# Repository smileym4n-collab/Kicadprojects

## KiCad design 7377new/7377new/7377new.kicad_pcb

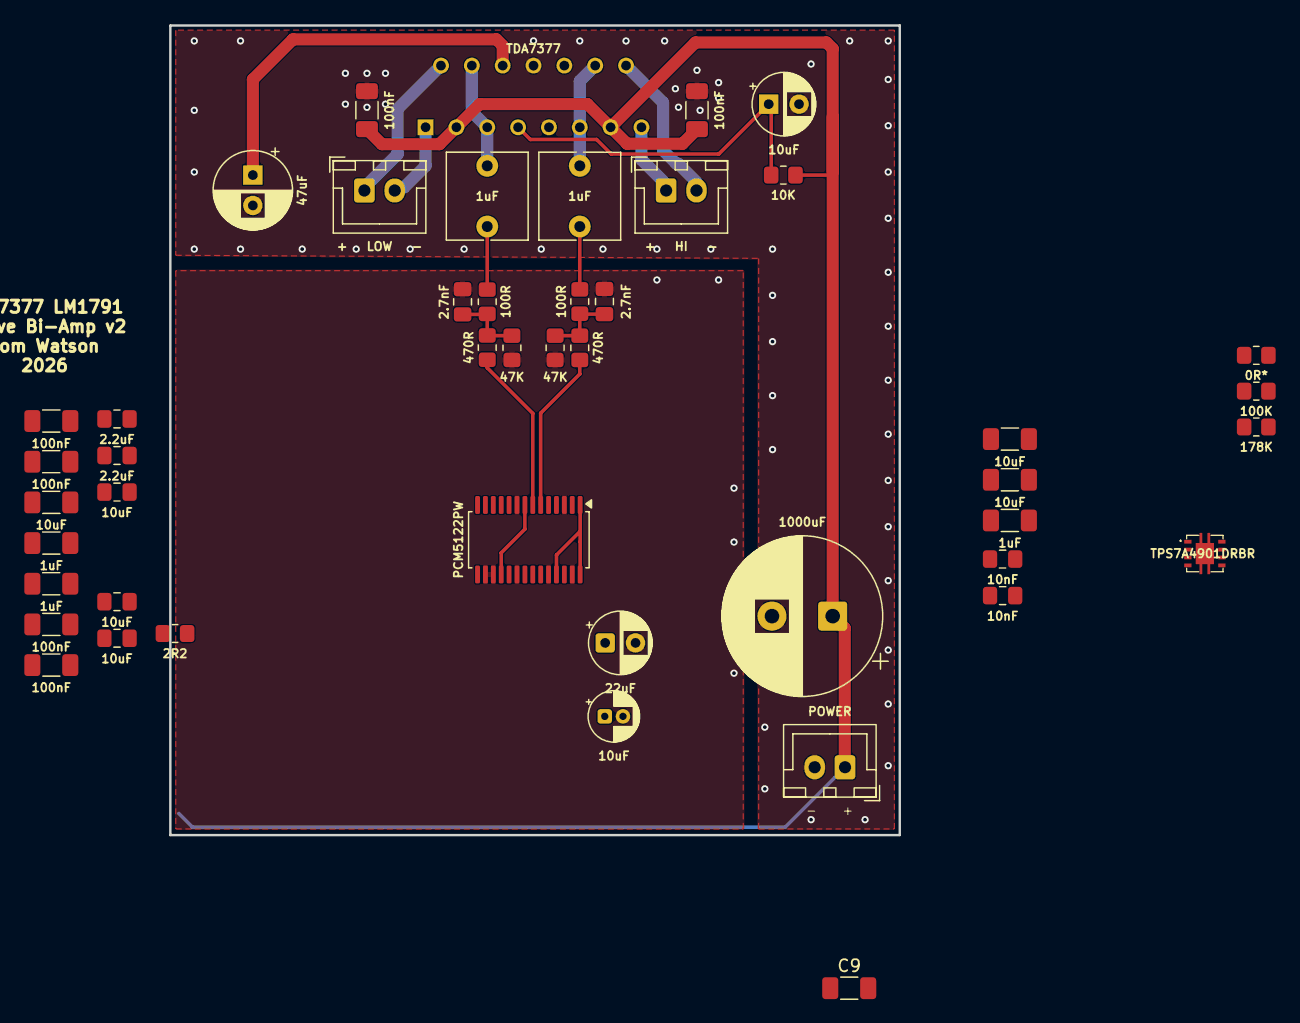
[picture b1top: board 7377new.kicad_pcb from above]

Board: 2 copper layers, 60.1 x 66.7 mm, 46 parts (0 on the bottom side), 24 nets.

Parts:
AMP1: TDA7377; AMP_TDA7377
C1, C2: 1uF; C_Rect_L7.0mm_W6.5mm_P5.00mm
C3, C9, C10, C28, C32, C66, C68: 100nF; C_1206_3216Metric_Pad1.33x1.80mm_HandSolder
C4: 1000uF; CP_Radial_D13.0mm_P5.00mm
C6, C18: 10nF; C_0805_2012Metric_Pad1.18x1.45mm_HandSolder
C11: 47uF; CP_Radial_D6.3mm_P2.50mm
C17: 10uF; CP_Radial_D5.0mm_P2.50mm
C27: 22uF; CP_Radial_D5.0mm_P2.50mm
C29, C30: 2.2uF; C_0805_2012Metric_Pad1.18x1.45mm_HandSolder
C31, C67, C69: 10uF; C_0805_2012Metric_Pad1.18x1.45mm_HandSolder
C33, C37, C39: 10uF; C_1206_3216Metric_Pad1.33x1.80mm_HandSolder
C34, C38: 2.7nF; C_0805_2012Metric_Pad1.18x1.45mm_HandSolder
C35, C36, C41: 1uF; C_1206_3216Metric_Pad1.33x1.80mm_HandSolder
C40: 10uF; CP_Radial_D4.0mm_P1.50mm
IC2: TPS7A4901DRBR
J1: + LOW -; JST_XH_B2B-XH-A_1x02_P2.50mm_Vertical
J2: + HI -; JST_XH_B2B-XH-A_1x02_P2.50mm_Vertical
J3: POWER; JST_XH_B2B-XH-A_1x02_P2.50mm_Vertical
R6, R7: 100R; R_0805_2012Metric_Pad1.20x1.40mm_HandSolder
R8, R9: 47K; R_0805_2012Metric_Pad1.20x1.40mm_HandSolder
R10: 0R*; R_0805_2012Metric_Pad1.20x1.40mm_HandSolder
R11: 100K; R_0805_2012Metric_Pad1.20x1.40mm_HandSolder
R12: 178K; R_0805_2012Metric_Pad1.20x1.40mm_HandSolder
R13: 10K; R_0805_2012Metric_Pad1.20x1.40mm_HandSolder
R31, R32: 470R; R_0805_2012Metric_Pad1.20x1.40mm_HandSolder
R61: 2R2; R_0805_2012Metric_Pad1.20x1.40mm_HandSolder
U12: PCM5122PW; TSSOP-28_4.4x9.7mm_P0.65mm

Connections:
/3V3: C18.2, C27.1, C28.1, C31.1, C39.2, C41.2, C66.1, C67.1, C68.1, C69.1, IC2.1 (OUT), R10.2, R12.2, U12.1 (CPVDD), U12.8 (AVDD), U12.18 (MODE2/MS), U12.25 (XSMT), U12.28 (DVDD)
/OUT-HI-DAC: C38.1, R7.1, R8.2, R32.1
/OUT-LOW-DAC: C34.1, R6.1, R9.2, R31.2
/VCC: AMP1.3 (VCC1), AMP1.13 (VCC2), C3.1, C4.1, C9.1, C10.1, C37.2, IC2.5 (EN), IC2.8 (IN), J3.1, R10.1, R13.2
GND: AMP1.8 (PWGND), AMP1.9 (SGND), C3.2, C4.2, C6.2, C9.2, C10.2, C11.2, C17.2, C27.2, C28.2, C29.2, C31.2, C32.2, C33.2, C34.2, C35.2, C36.2, C37.1, C38.2, C39.1, C40.2, C41.1, C66.2, C67.2, C68.2, C69.2, IC2.4 (GND), IC2.9 (EP_1), IC2.10 (EP_2), IC2.11 (EP_3), IC2.12 (EP_4), IC2.13 (EP_5), J3.2, R8.1, R9.1, R11.2, U12.3 (CPGND), U12.9 (AGND), U12.16 (ADR2/GPIO2/DOUT), U12.17 (MODE1), U12.20 (SCK), U12.24 (ADR1/MISO/FMT), U12.27 (DGND)
unnamed: AMP1.4 (IN1), AMP1.5 (IN2), C1.2
unnamed: AMP1.11 (IN4), AMP1.12 (IN3), C2.2
unnamed: AMP1.1 (OUT1), J1.2
unnamed: AMP1.2 (OUT2), J1.1
unnamed: AMP1.15 (OUT3), J2.1
unnamed: AMP1.14 (OUT4), J2.2
unnamed: AMP1.7 (STANDBY), C17.1, R13.1
unnamed: AMP1.6 (SVR), C11.1
unnamed: C1.1, R6.2
unnamed: C2.1, R7.2
unnamed: C18.1, IC2.2 (FB), R11.1, R12.1
unnamed: C6.1, IC2.6 (NR/SS)
unnamed: C36.1, C40.1, R61.2
unnamed: C30.2, U12.4 (CAPM)
unnamed: C30.1, U12.2 (CAPP)
unnamed: C32.1, C33.1, U12.26 (LDOO)
unnamed: R32.2, U12.6 (OUTL)
unnamed: R31.1, U12.7 (OUTR)
unnamed: C29.1, U12.5 (VNEG)

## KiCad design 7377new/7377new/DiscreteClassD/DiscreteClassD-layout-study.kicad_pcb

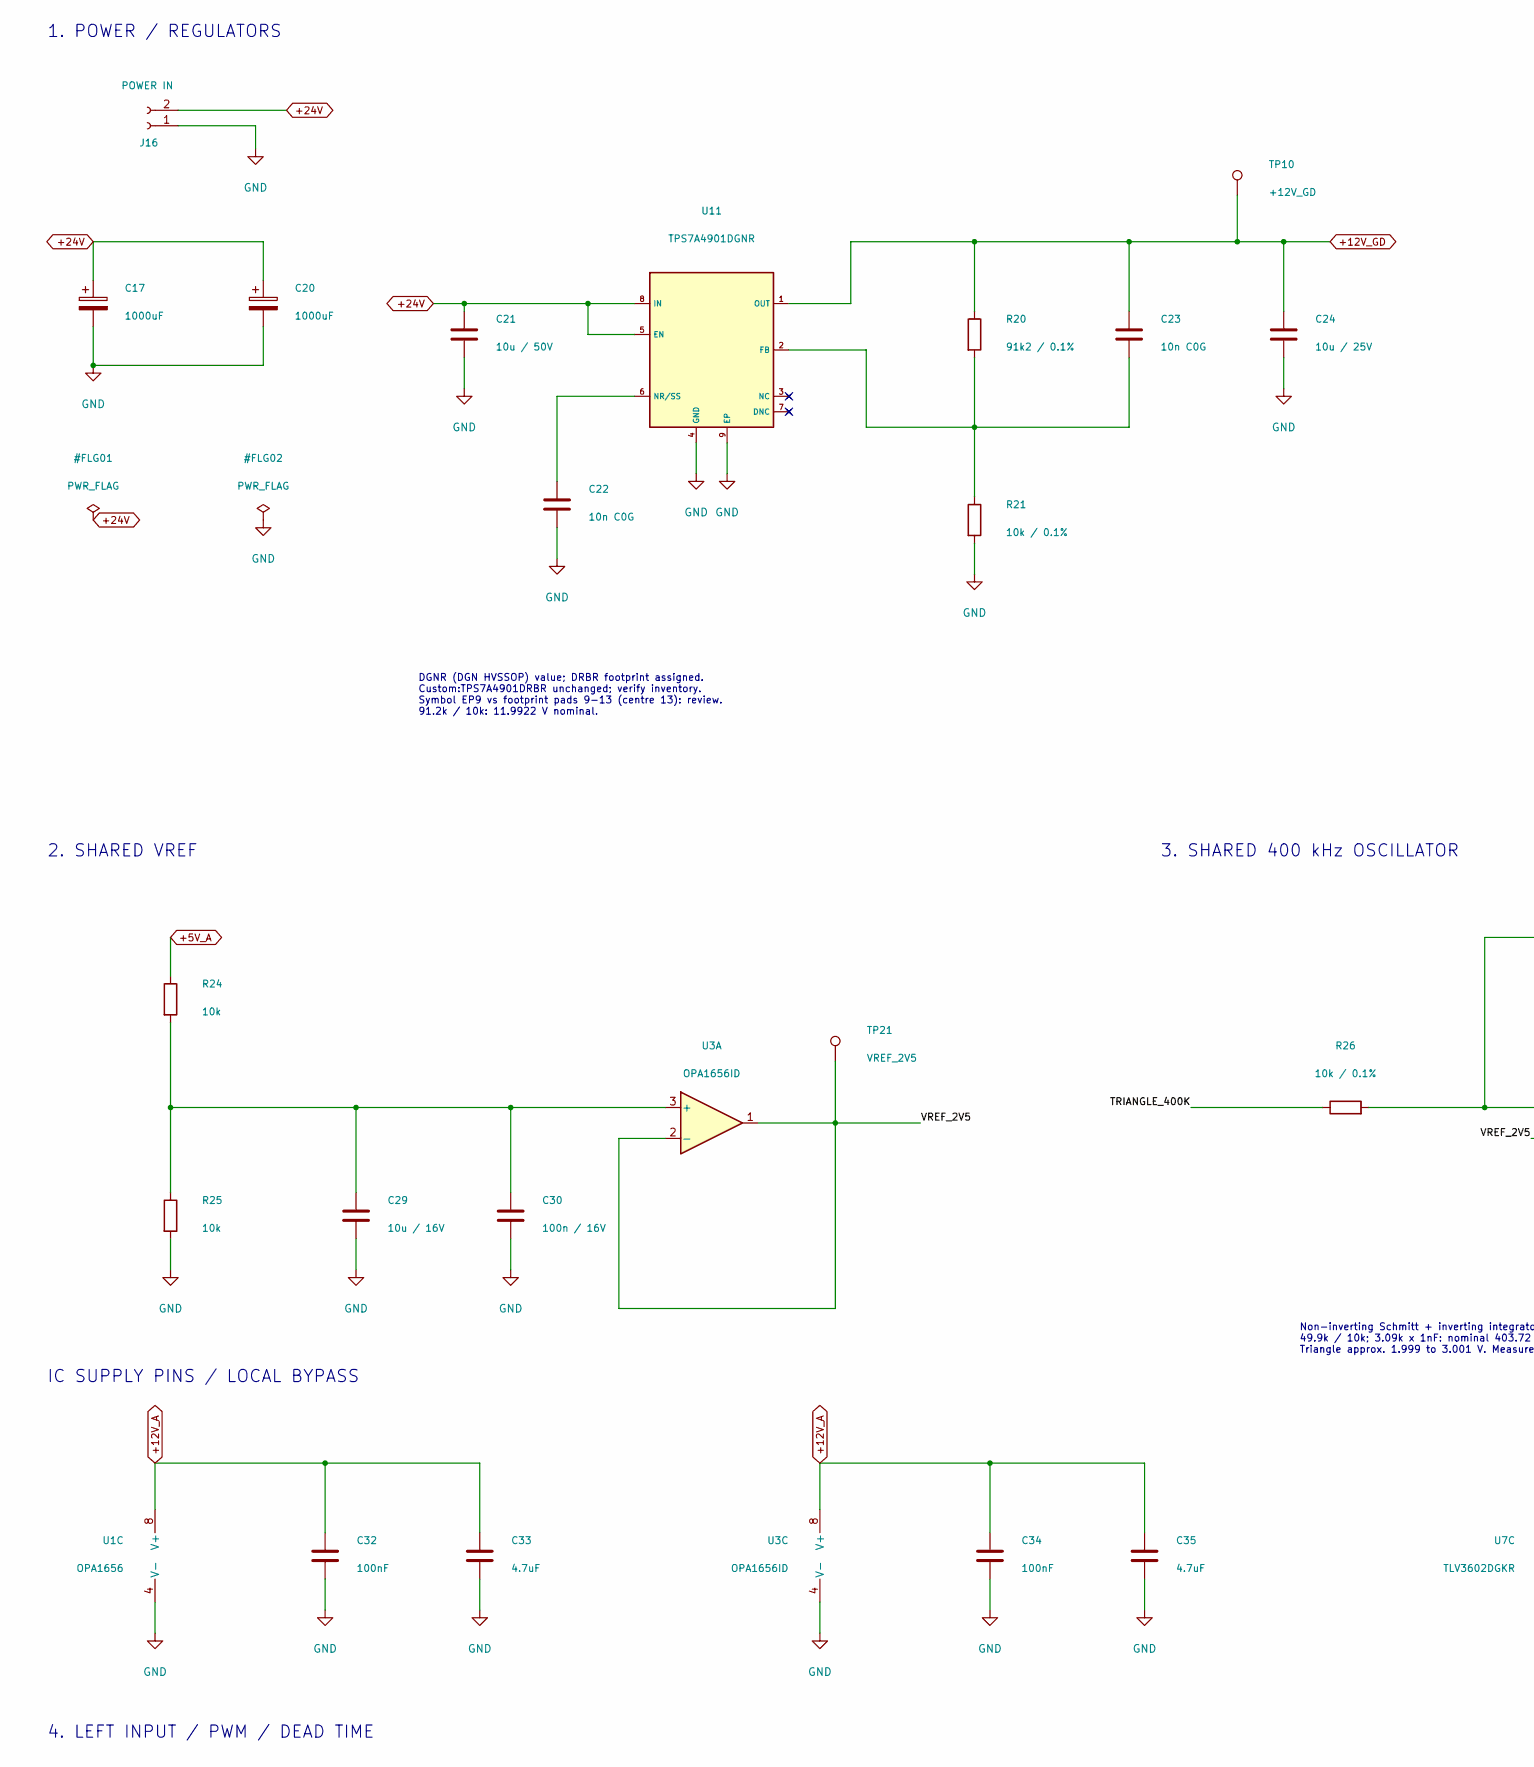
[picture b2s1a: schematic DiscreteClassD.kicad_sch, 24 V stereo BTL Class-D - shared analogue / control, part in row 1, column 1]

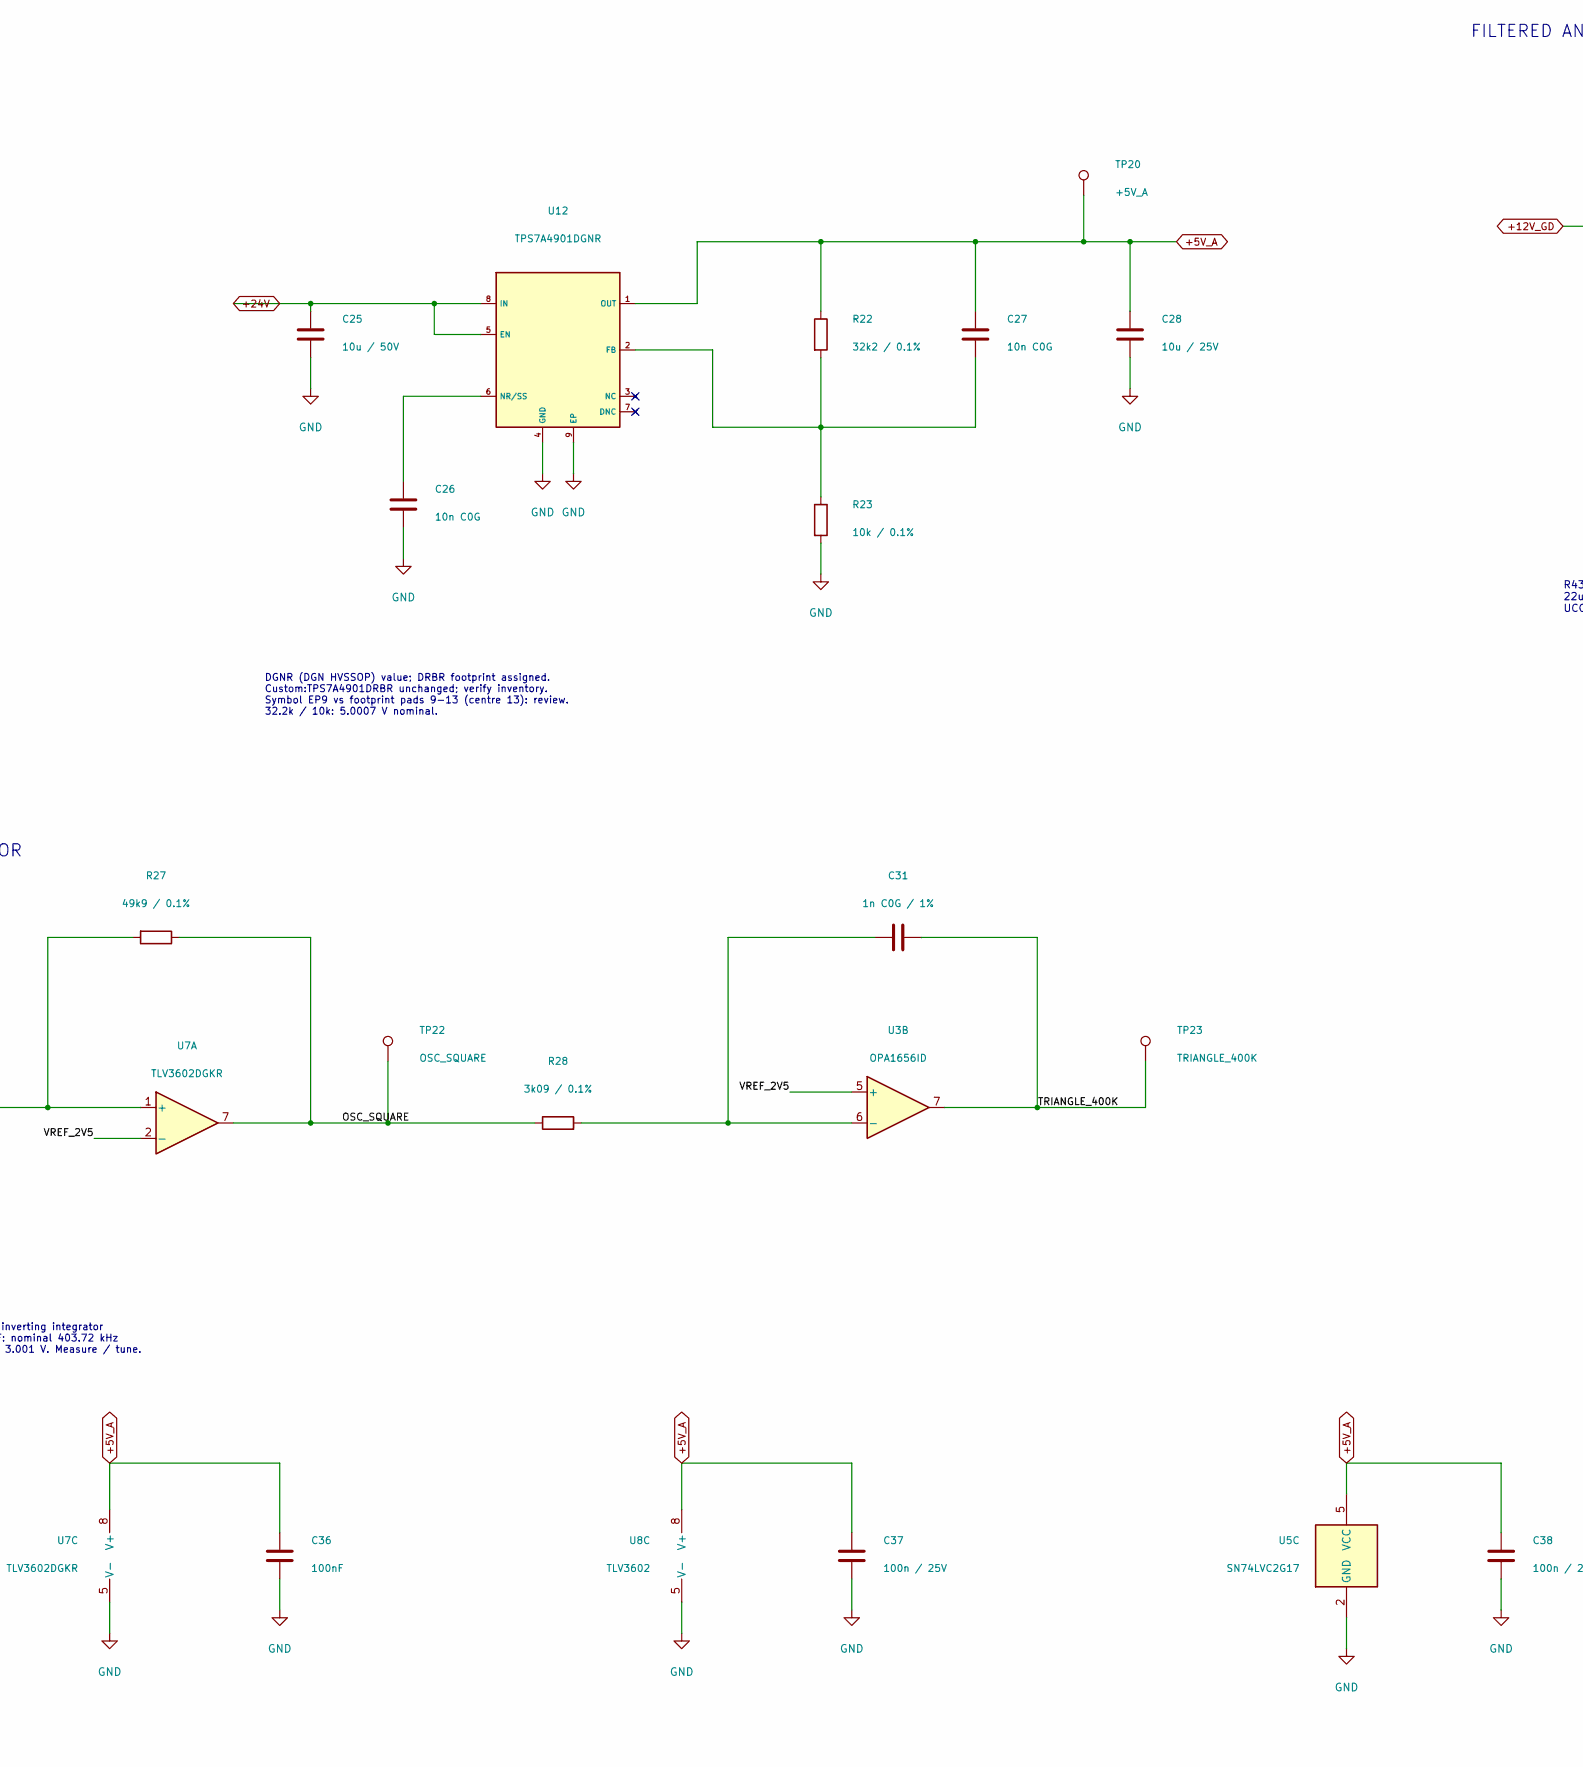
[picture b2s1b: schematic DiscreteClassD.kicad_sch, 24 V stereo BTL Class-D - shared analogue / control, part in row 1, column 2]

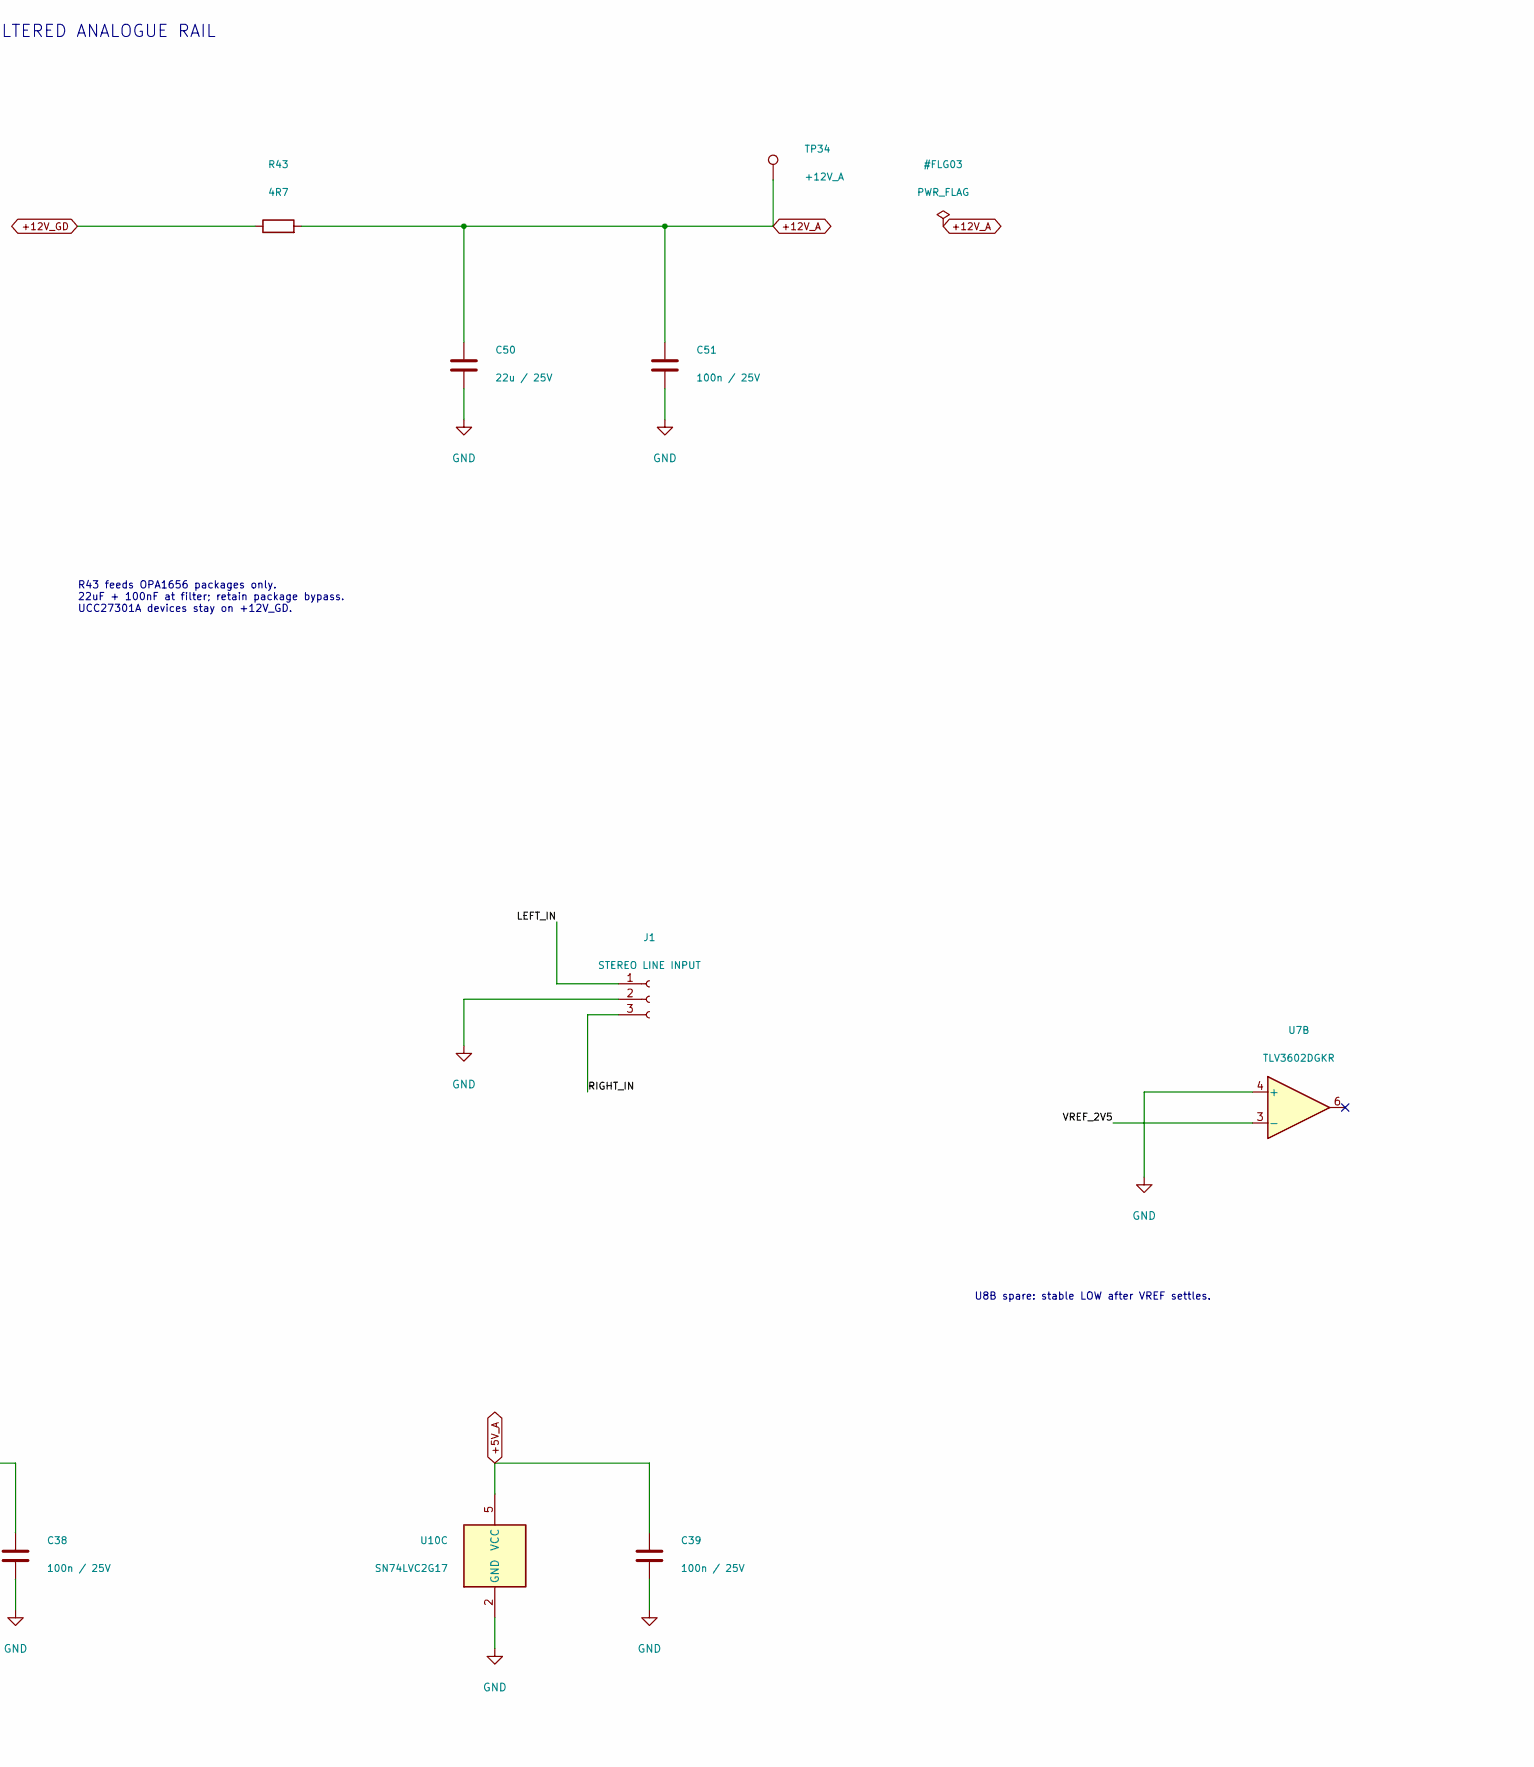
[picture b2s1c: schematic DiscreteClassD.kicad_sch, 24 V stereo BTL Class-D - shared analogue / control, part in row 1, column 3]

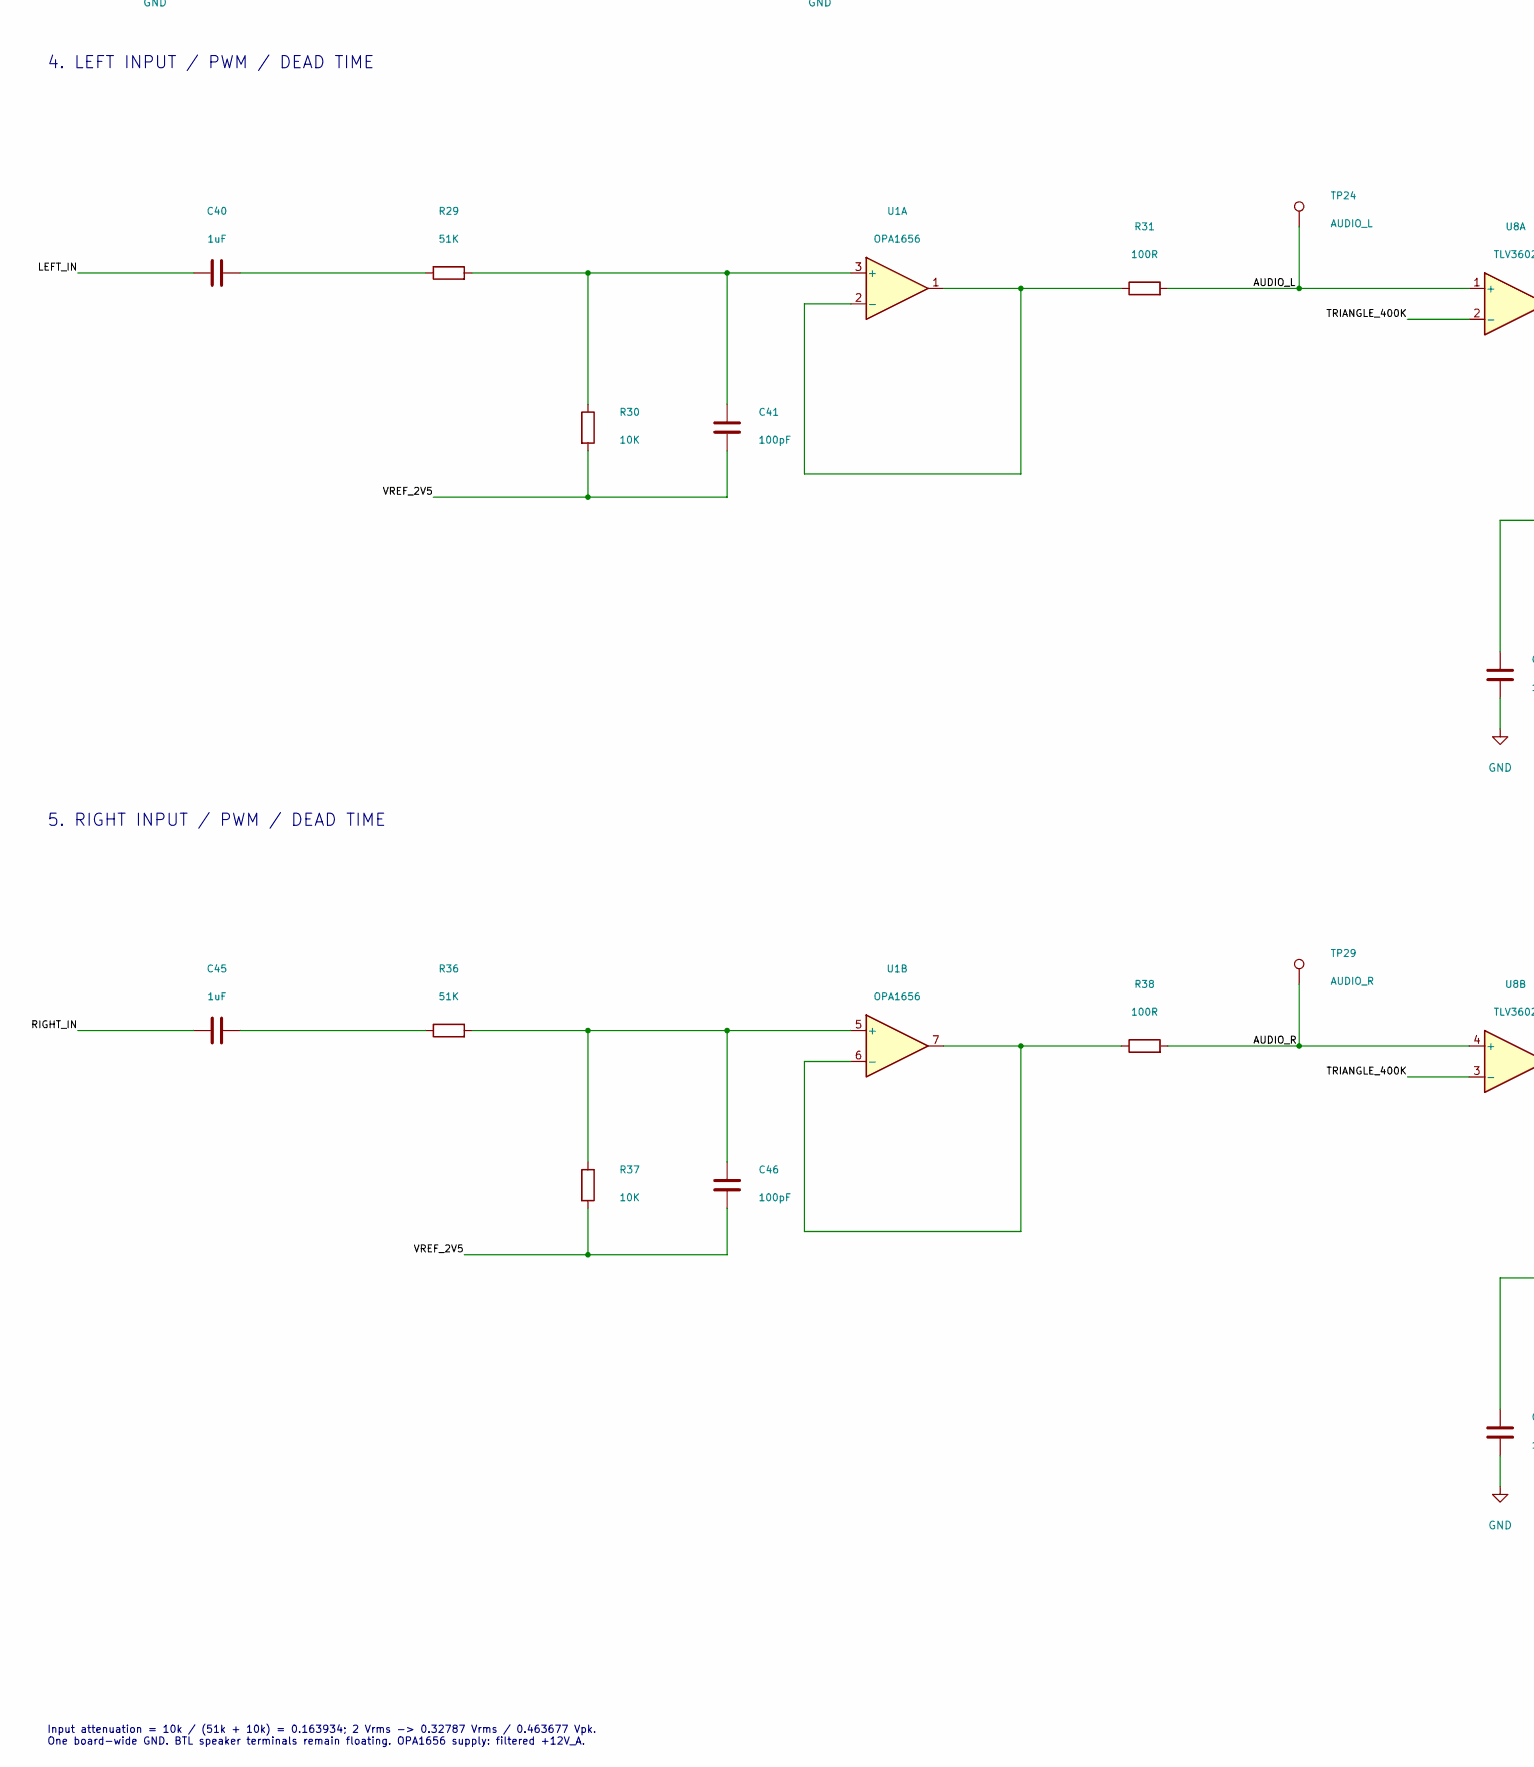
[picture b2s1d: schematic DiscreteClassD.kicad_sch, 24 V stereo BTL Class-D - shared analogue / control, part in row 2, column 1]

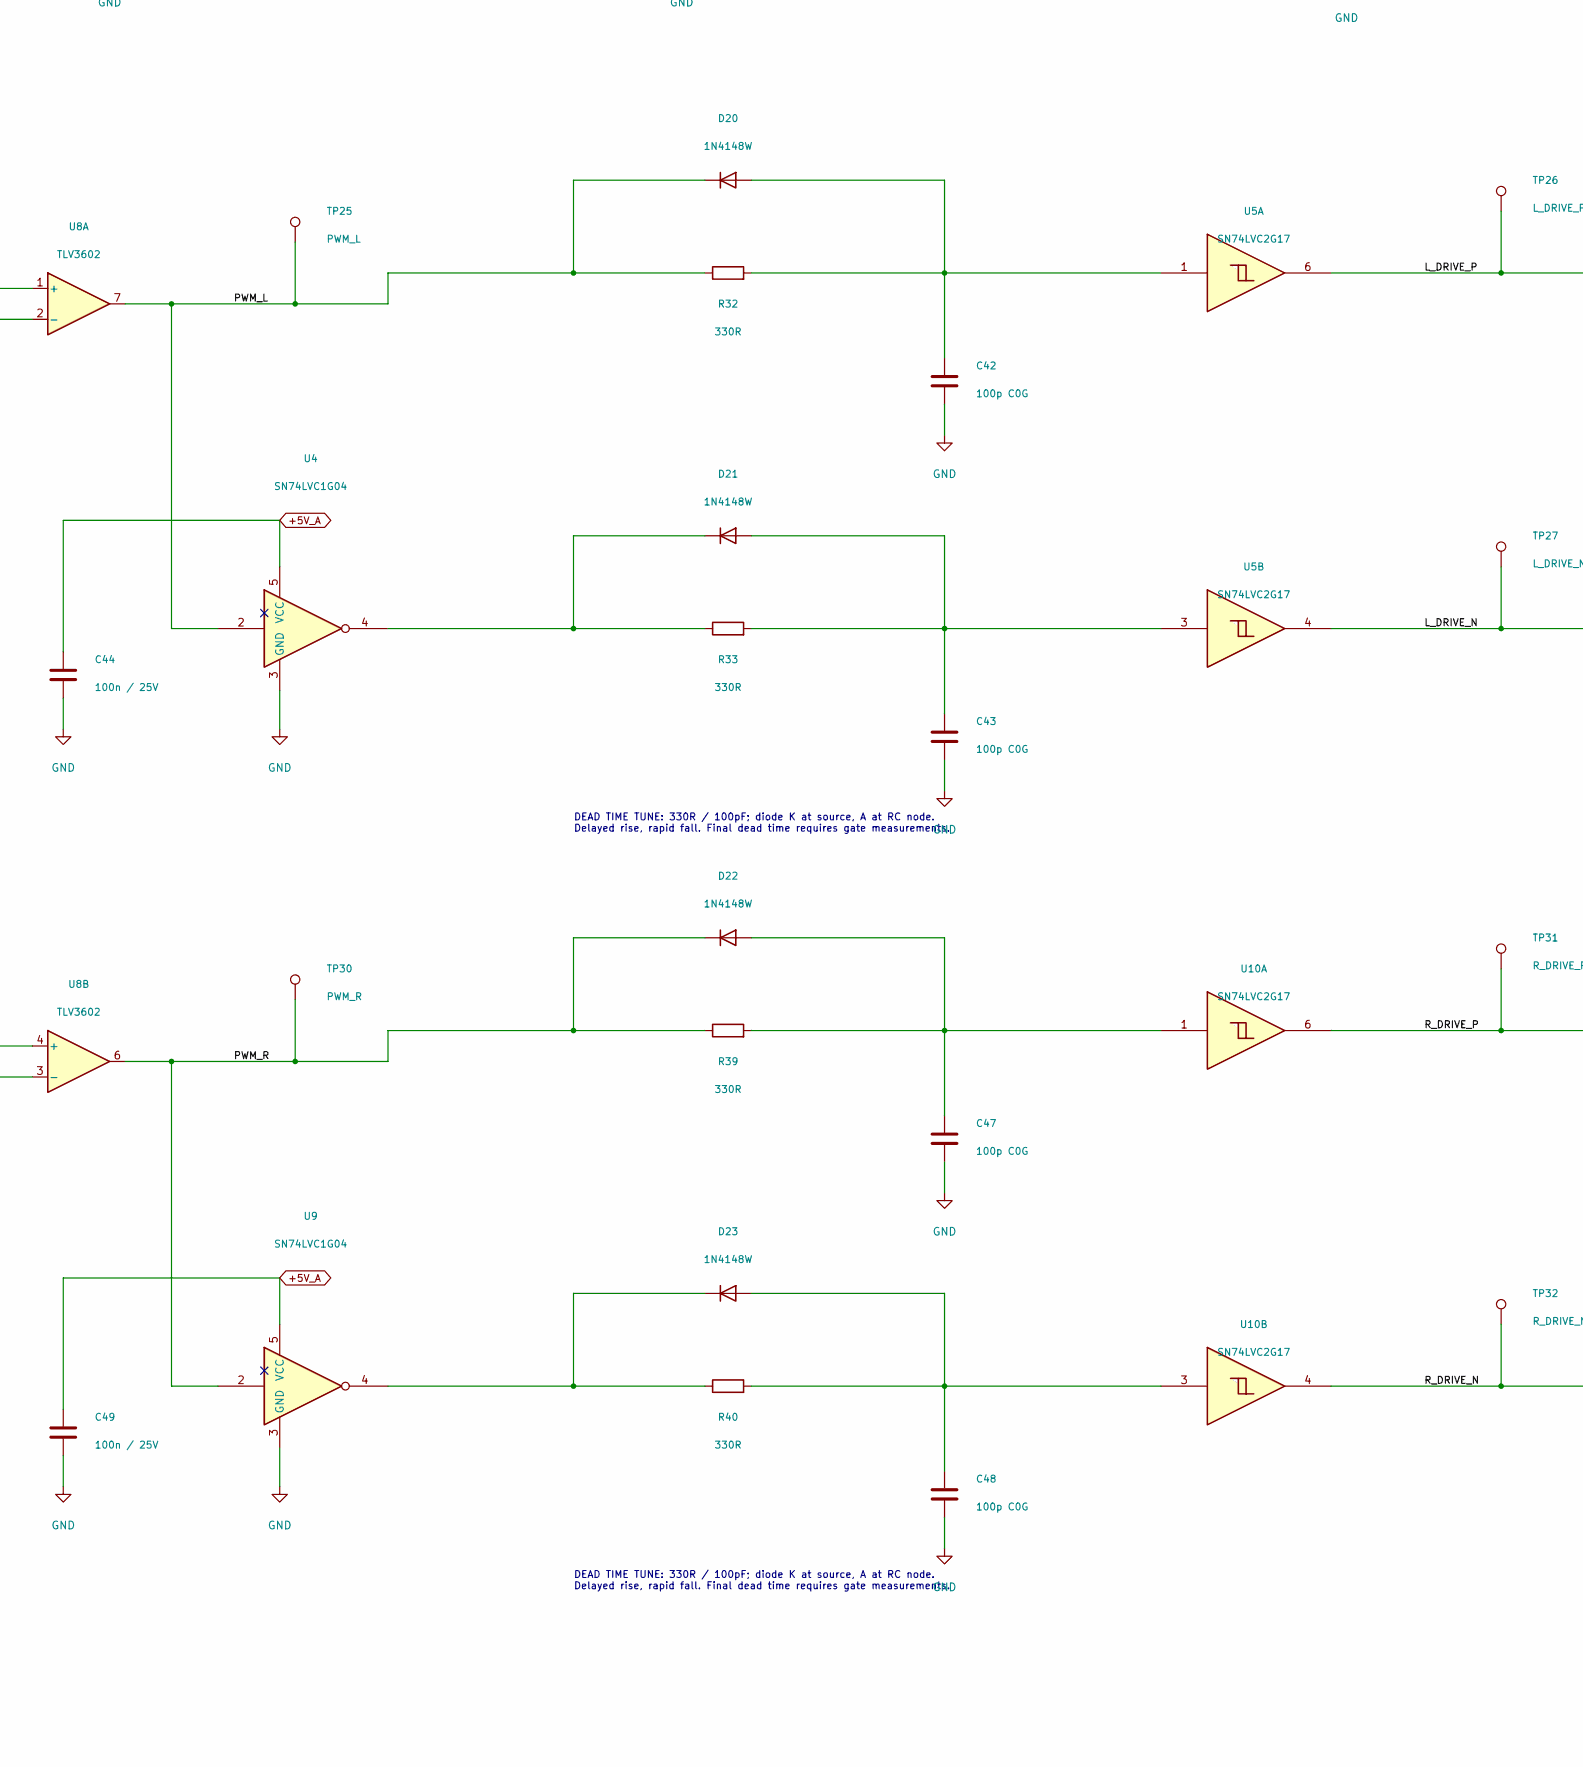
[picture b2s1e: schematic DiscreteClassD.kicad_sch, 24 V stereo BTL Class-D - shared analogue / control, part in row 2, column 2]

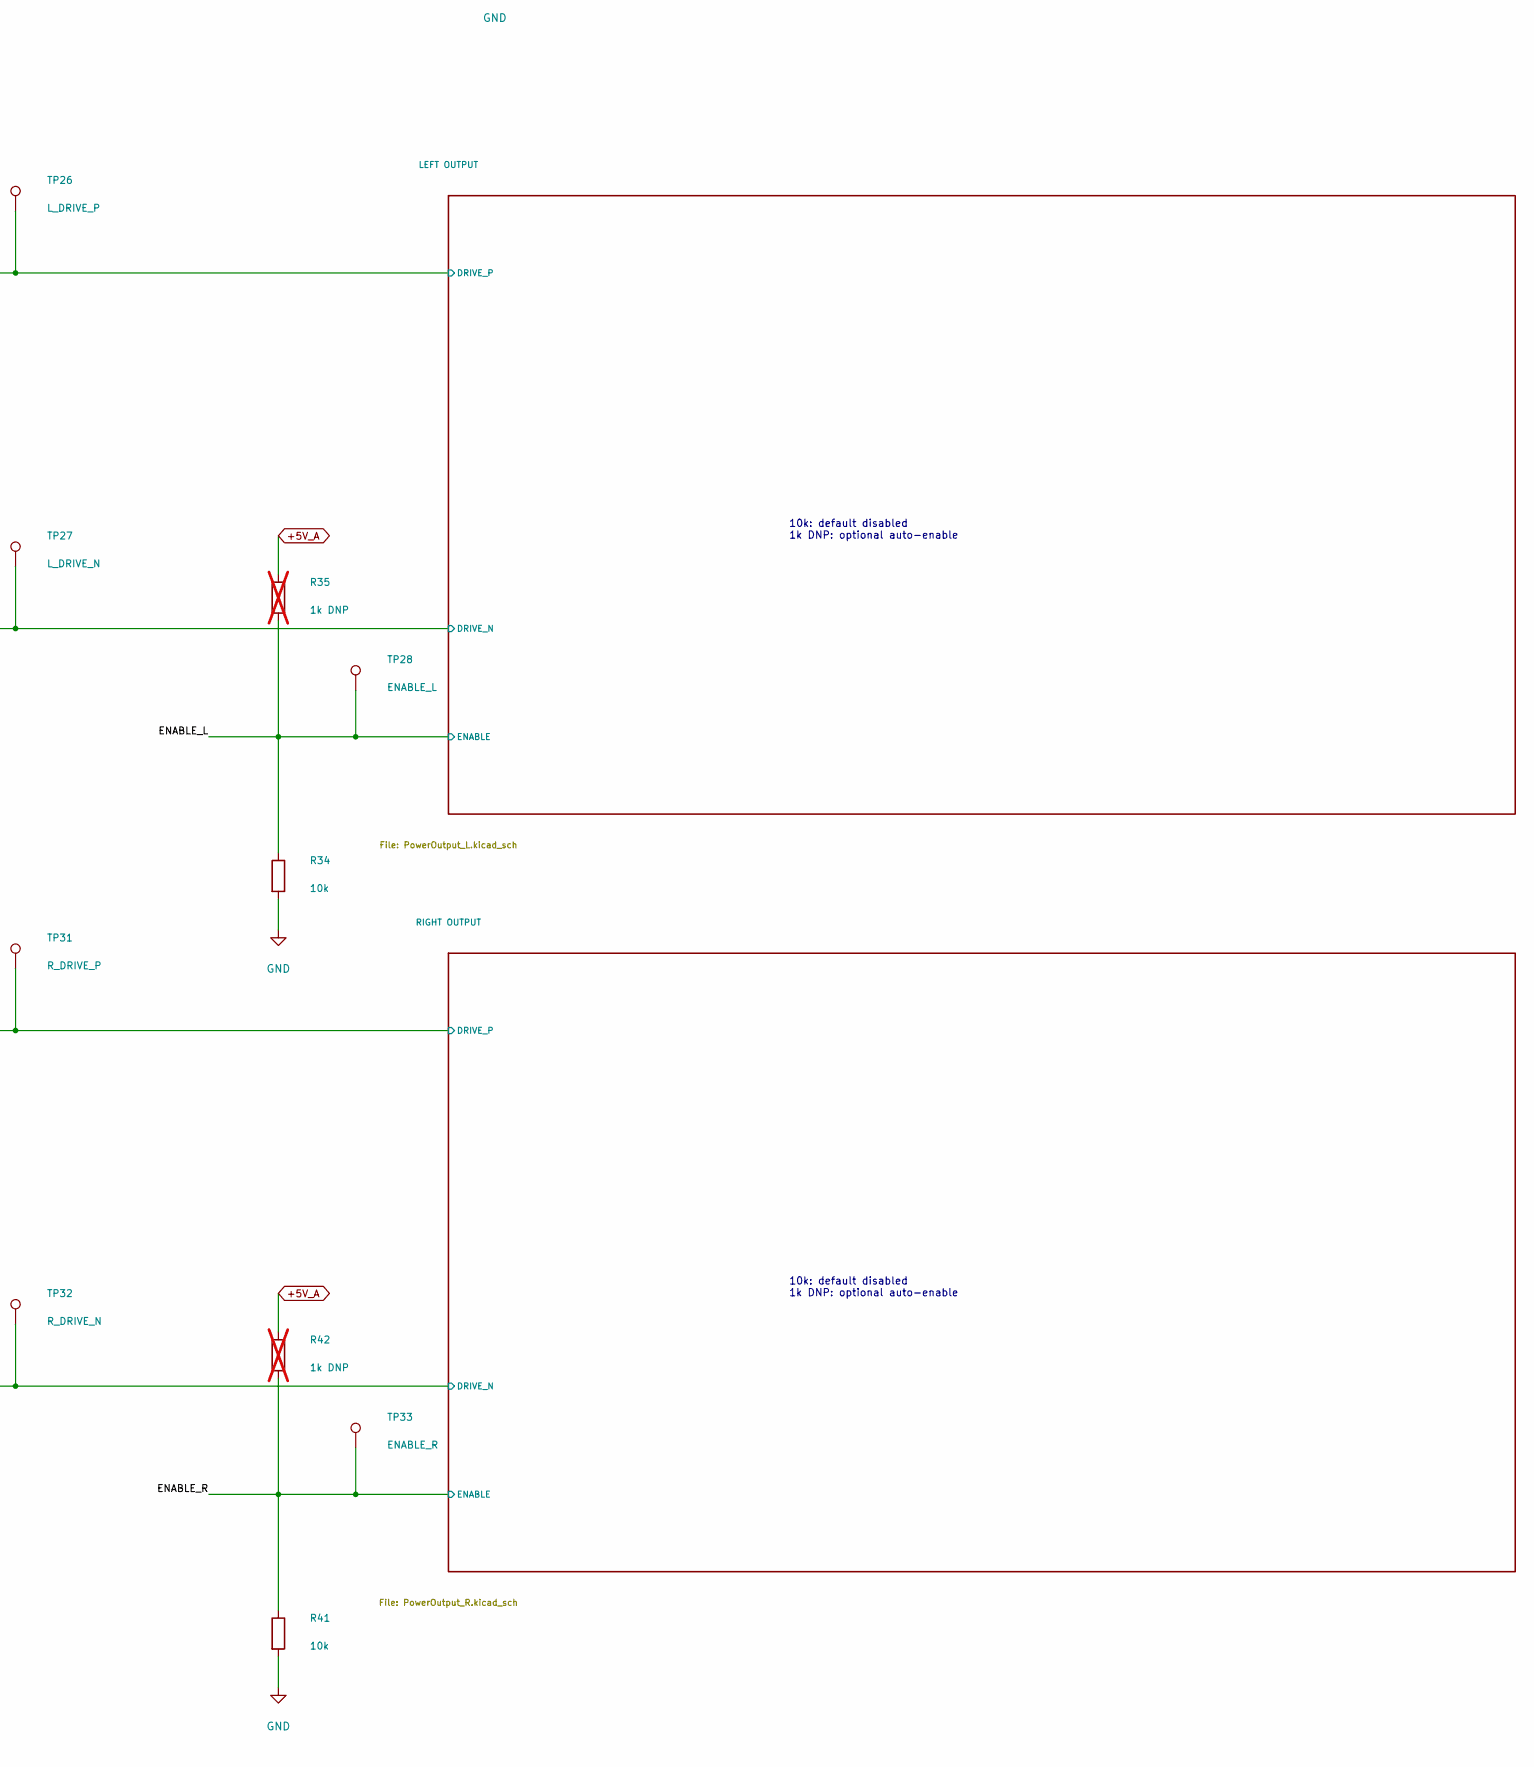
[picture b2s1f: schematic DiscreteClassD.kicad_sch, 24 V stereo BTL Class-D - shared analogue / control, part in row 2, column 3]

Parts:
C17, C20: 1000uF; CP_Radial_D12.5mm_P5.00mm; MPN EEUFR1V102
C21, C25: 10u / 50V; C_1210_3225Metric
C22, C23, C26, C27: 10n C0G; C_0805_2012Metric
C24, C28: 10u / 25V; C_1210_3225Metric
C29: 10u / 16V; C_0805_2012Metric
C30: 100n / 16V; C_0805_2012Metric
C31: 1n C0G / 1%; C_0805_2012Metric
C32, C34: 100nF; C_1206_3216Metric_Pad1.33x1.80mm_HandSolder
C33, C35: 4.7uF; C_0805_2012Metric
C36: 100nF; C_0805_2012Metric
C37, C38, C39, C44, C49, C51: 100n / 25V; C_0805_2012Metric
C40, C45: 1uF; C_Rect_L7.2mm_W5.5mm_P5.00mm_FKS2_FKP2_MKS2_MKP2
C41, C46: 100pF; C_0805_2012Metric
C42, C43, C47, C48: 100p C0G; C_0805_2012Metric
C50: 22u / 25V; C_1210_3225Metric
D20, D21, D22, D23: 1N4148W; D_SOD-123
J1: STEREO LINE INPUT; JST_XH_B3B-XH-A_1x03_P2.50mm_Vertical
J16: POWER IN; Molex_KK-396_A-41791-0002_1x02_P3.96mm_Vertical
R20: 91k2 / 0.1%; R_0805_2012Metric
R21, R23, R26: 10k / 0.1%; R_0805_2012Metric
R22: 32k2 / 0.1%; R_0805_2012Metric
R24, R25, R34, R41: 10k; R_0805_2012Metric
R27: 49k9 / 0.1%; R_0805_2012Metric
R28: 3k09 / 0.1%; R_0805_2012Metric
R29, R36: 51K; R_0805_2012Metric
R30, R37: 10K; R_0805_2012Metric
R31, R38: 100R; R_0805_2012Metric
R32, R33, R39, R40: 330R; R_0805_2012Metric
R35, R42: 1k DNP; R_0805_2012Metric; not fitted
R43: 4R7; R_0805_2012Metric
TP10: +12V_GD; TestPoint_Pad_D1.5mm
TP20: +5V_A; TestPoint_Pad_D1.5mm
TP21: VREF_2V5; TestPoint_Pad_D1.5mm
TP22: OSC_SQUARE; TestPoint_Pad_D1.5mm
TP23: TRIANGLE_400K; TestPoint_Pad_D1.5mm
TP24: AUDIO_L; TestPoint_Pad_D1.5mm
TP25: PWM_L; TestPoint_Pad_D1.5mm
TP26: L_DRIVE_P; TestPoint_Pad_D1.5mm
TP27: L_DRIVE_N; TestPoint_Pad_D1.5mm
TP28: ENABLE_L; TestPoint_Pad_D1.5mm
TP29: AUDIO_R; TestPoint_Pad_D1.5mm
TP30: PWM_R; TestPoint_Pad_D1.5mm
TP31: R_DRIVE_P; TestPoint_Pad_D1.5mm
TP32: R_DRIVE_N; TestPoint_Pad_D1.5mm
TP33: ENABLE_R; TestPoint_Pad_D1.5mm
TP34: +12V_A; TestPoint_Pad_D1.5mm
U1: OPA1656; SOIC-8_3.9x4.9mm_P1.27mm
U3: OPA1656ID; SOIC-8_3.9x4.9mm_P1.27mm
U4, U9: SN74LVC1G04; SOT-23-5
U5, U10: SN74LVC2G17; SOT-23-6
U7: TLV3602DGKR; VSSOP-8_3x3mm_P0.65mm
U8: TLV3602; VSSOP-8_3x3mm_P0.65mm
U11, U12: TPS7A4901DGNR; TPS7A4901DRBR

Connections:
+5V_A: C27.1, C28.1, C36.1, C37.1, C38.1, C39.1, C44.1, C49.1, R22.1, R24.1, R35.1, R42.1, TP20.1 (1_1), U4.5 (VCC), U5.5 (VCC), U7.8 (V+), U8.8 (V+), U9.5 (VCC), U10.5 (VCC), U12.1 (OUT)
+12V_A: C32.1, C33.1, C34.1, C35.1, C50.1, C51.1, R43.2, TP34.1 (1_1), U1.8 (V+), U3.8 (V+)
+12V_GD: C23.1, C24.1, R20.1, R43.1, TP10.1 (1_1), U11.1 (OUT); also elsewhere on the board
+24V: C17.1, C20.1, C21.1, C25.1, J16.2, U11.5 (EN), U11.8 (IN), U12.5 (EN), U12.8 (IN); also elsewhere on the board
/AUDIO_L: R31.2, TP24.1 (1_1), U8.1 (+)
/AUDIO_R: R38.2, TP29.1 (1_1), U8.4 (+)
/ENABLE_R: R41.1, R42.2, TP33.1 (1_1); also elsewhere on the board
/LEFT_IN: C40.1, J1.1
/OSC_SQUARE: R27.1, R28.1, TP22.1 (1_1), U7.7
/PWM_L: D20.1 (K), R32.1, TP25.1 (1_1), U4.2, U8.7
/PWM_R: D22.1 (K), R39.1, TP30.1 (1_1), U8.6, U9.2
/RIGHT_IN: C45.1, J1.3
/R_DRIVE_N: TP32.1 (1_1), U10.4; also elsewhere on the board
/R_DRIVE_P: TP31.1 (1_1), U10.6; also elsewhere on the board
/TRIANGLE_400K: C31.2, R26.1, TP23.1 (1_1), U3.7, U8.2 (-), U8.3 (-)
/VREF_2V5: C41.2, C46.2, R30.2, R37.2, TP21.1 (1_1), U3.1, U3.2 (-), U3.5 (+), U7.2 (-), U7.3 (-)
GND: C17.2, C20.2, C21.2, C22.2, C24.2, C25.2, C26.2, C28.2, C29.2, C30.2, C32.2, C33.2, C34.2, C35.2, C36.2, C37.2, C38.2, C39.2, C42.2, C43.2, C44.2, C47.2, C48.2, C49.2, C50.2, C51.2, J1.2, J16.1, R21.2, R23.2, R25.2, R34.2, R41.2, U1.4 (V-), U3.4 (V-), U4.3 (GND), U5.2 (GND), U7.4 (+), U7.5 (V-), U8.5 (V-), U9.3 (GND), U10.2 (GND), U11.4 (GND), U11.9 (EP), U12.4 (GND), U12.9 (EP); also elsewhere on the board
unnamed: C40.2, R29.1
unnamed: C45.2, R36.1
unnamed: C42.1, D20.2 (A), R32.2, U5.1 (1A)
unnamed: C43.1, D21.2 (A), R33.2, U5.3 (2A)
unnamed: D21.1 (K), R33.1, U4.4
unnamed: C47.1, D22.2 (A), R39.2, U10.1
unnamed: C48.1, D23.2 (A), R40.2, U10.3
unnamed: D23.1 (K), R40.1, U9.4
unnamed: C41.1, R29.2, R30.1, U1.3 (+)
unnamed: R31.1, U1.1, U1.2 (-)
unnamed: C46.1, R36.2, R37.1, U1.5 (+)
unnamed: R38.1, U1.6 (-), U1.7
unnamed: C29.1, C30.1, R24.2, R25.1, U3.3 (+)
unnamed: C31.1, R28.2, U3.6 (-)
unnamed: R26.2, R27.2, U7.1 (+)
unnamed: C23.2, R20.2, R21.1, U11.2 (FB)
unnamed: C22.1, U11.6 (NR/SS)
unnamed: C27.2, R22.2, R23.1, U12.2 (FB)
unnamed: C26.1, U12.6 (NR/SS)

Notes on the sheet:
FILTERED ANALOGUE RAIL
Non-inverting Schmitt + inverting integrator 49.9k / 10k; 3.09k x 1nF: nominal 403.72 kHz Triangle approx. 1.999 to 3.001 V. Measure / tune.
10k: default disabled 1k DNP: optional auto-enable
DGNR (DGN HVSSOP) value; DRBR footprint assigned. Custom:TPS7A4901DRBR unchanged; verify inventory. Symbol EP9 vs footprint pads 9-13 (centre 13): review. 91.2k / 10k: 11.9922 V nominal.
DEAD TIME TUNE: 330R / 100pF; diode K at source, A at RC node. Delayed rise, rapid fall. Final dead time requires gate measurements.
R43 feeds OPA1656 packages only. 22uF + 100nF at filter; retain package bypass. UCC27301A devices stay on +12V_GD.
2. SHARED VREF
5. RIGHT INPUT / PWM / DEAD TIME
U8B spare: stable LOW after VREF settles.
1. POWER / REGULATORS
4. LEFT INPUT / PWM / DEAD TIME
3. SHARED 400 kHz OSCILLATOR
Input attenuation = 10k / (51k + 10k) = 0.163934; 2 Vrms -> 0.32787 Vrms / 0.463677 Vpk. One board-wide GND. BTL speaker terminals remain floating. OPA1656 supply: filtered +12V_A.
DGNR (DGN HVSSOP) value; DRBR footprint assigned. Custom:TPS7A4901DRBR unchanged; verify inventory. Symbol EP9 vs footprint pads 9-13 (centre 13): review. 32.2k / 10k: 5.0007 V nominal.
IC SUPPLY PINS / LOCAL BYPASS
